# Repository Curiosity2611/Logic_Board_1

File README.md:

## Full Documentation

I will amend this documentation as the project progresses.

**Logic Board 1 Variants:**

- Logic Board 1A (No wireless)
	- LB1A_DCA7M4_R512MB_F4GB (Dual Core A7 + M4, 512MB DDR3L RAM, 4GB eMMC)
	- LB1A_SCA7M4_R512MB_F4GB (Single Core A7 + M4, 512MB DDR3L RAM, 4GB eMMC)
- Logic Board 1B (Only BLE 5.0)
	- LB1B_DCA7M4_R512MB_F4GB (Dual Core A7 + M4, 512MB DDR3L RAM, 4GB eMMC)
	- LB1B_SCA7M4_R512MB_F4GB (Single Core A7 + M4, 512MB DDR3L RAM, 4GB eMMC)
- Logic Board 1C (Only WiFi)
	- LB1B_DCA7M4_R512MB_F4GB (Dual Core A7 + M4, 512MB DDR3L RAM, 4GB eMMC)
	- LB1B_SCA7M4_R512MB_F4GB (Single Core A7 + M4, 512MB DDR3L RAM, 4GB eMMC)
- Logic Board 1D (WiFi + BLE 5.0)
	- LB1B_DCA7M4_R512MB_F4GB (Dual Core A7 + M4, 512MB DDR3L RAM, 4GB eMMC)
	- LB1B_SCA7M4_R512MB_F4GB (Single Core A7 + M4, 512MB DDR3L RAM, 4GB eMMC)

**Logic Board I/O:**

Common expansion Board for all Logic Board 1 Variants. 

## A little background about the project

How it all started.

### Problem

Recently I came accross the ST's line of Microprocessors and I felt it fascinating. I personally felt this is one of the best Microprocessor out there in the market as it is the combination of an MPU and an  MCU. This combination has many use cases and I felt I should try this out. So I bought STM32MP157C-DK2 development board and started experimenting! <br>

Previously I had little experience working on couple of popular linux dev boards like the BeagleBone Black
and the Raspberry Pi. They are both fantastic boards to work with and they both have good community support. But while working with them, I realised a few bunch of problems:

- **Raspberry Pi Compute Module 4 + IO Board**
    - CM4 is easy to use but not ideal for mass production.
    - No support for analog signals at hardware level.
    - Software PWM possible but not very precise.
    - Cannot support real time application or processing.
    - Not fully open-source and very minimum customization possible. <br>
<br>

- **BeagleBone Black**
    - Easy to use but user has to own build hardware for production.
    - PRUs make RT applications possible but super difficult to use.
    - Cannot support MIPI-DSI and HD graphics.
    - Programming PRUs is not an easy task.

### Solution

**Best of both worlds**

**Hello World STM32MP1 !!**

- Board design inspired from Raspberry Pi Compute Module 4 and CM4 IO board.
- Operating system derived from Beaglebone Black with implementation of Bonescript Library and Cloud9 IDE.
- Footprint compatible Single or dual Cortex-A7 Processors + dedicated Cortex-M4 core for real-time and low-power applications.
- Support for MIPI-DSI display for HMI applications.
- Fully open-source Hardware and Software.

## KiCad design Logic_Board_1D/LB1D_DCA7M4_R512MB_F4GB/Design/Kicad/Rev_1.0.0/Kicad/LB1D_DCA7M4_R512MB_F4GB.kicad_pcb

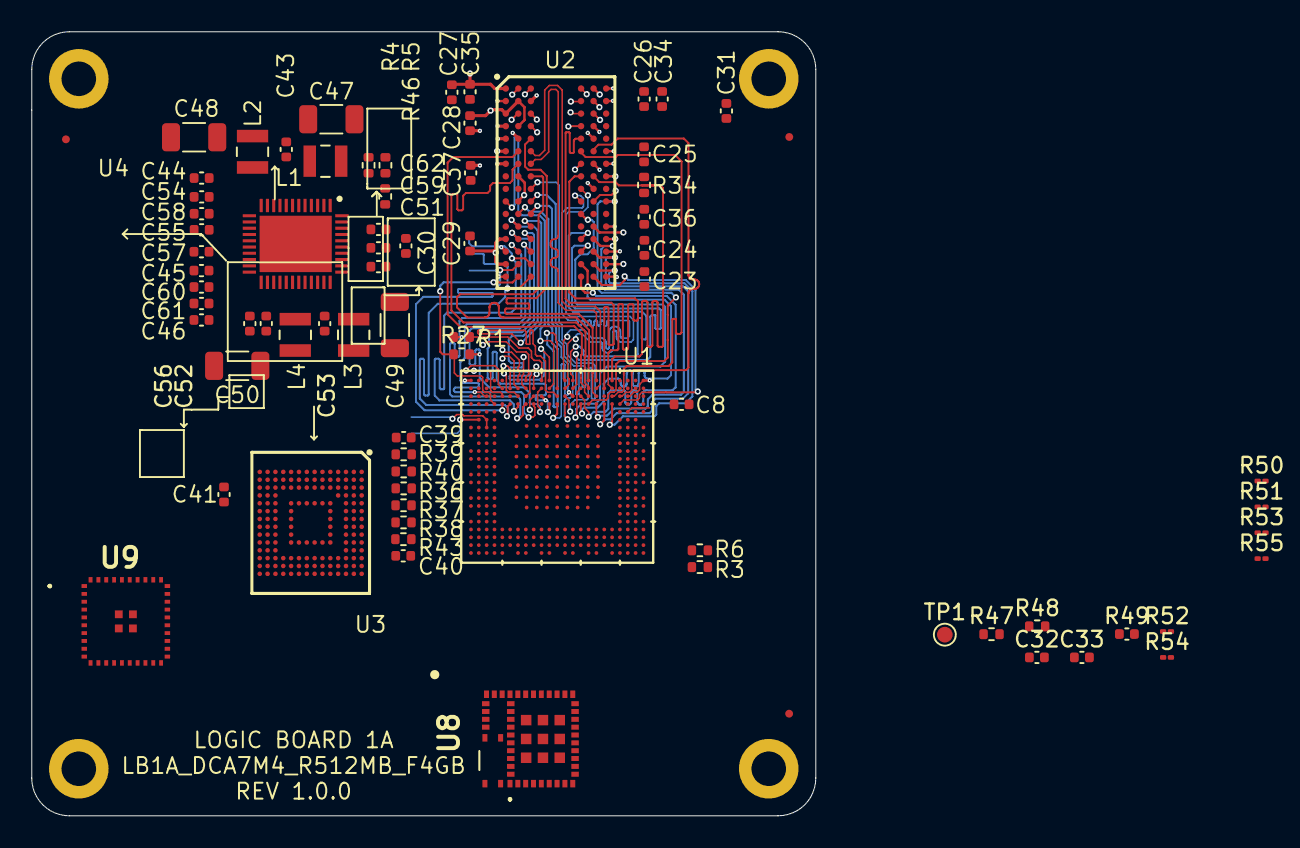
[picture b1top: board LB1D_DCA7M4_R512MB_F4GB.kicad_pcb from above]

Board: 4 copper layers, 50.0 x 50.0 mm, 157 parts (0 on the bottom side), 213 nets.

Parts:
C1, C2, C5, C6, C51, C52, C63, C64, C65, C66, C67, C68, C69, C70, C72, C73, C74: 1uF; C_0402_1005Metric
C3, C4, C8, C9, C10, C11, C12, C13, C14, C15, C16, C17, C18, C19, C20, C23, C24, C25, C26, C27, C28, C29, C30, C31, C36, C37, C38, C39, C40: 100nF; C_0402_1005Metric
C7: 10nF; C_0402_1005Metric
C21, C22, C32, C34, C35, C41, C43, C44, C45, C46, C54: 10uF; C_0402_1005Metric
C33, C75, C76, C77: 10pF; C_0402_1005Metric
C42: 2.2uF; C_0402_1005Metric
C47, C48, C49, C50: 22uF; C_1206_3216Metric
C53, C55, C56, C57, C58, C59, C60, C61, C62: 4.7uF; C_0402_1005Metric
FID1, FID2, FID3, FID4, FID5, FID6: Fiducial; Fiducial_0.5mm_Mask1.5mm
H1, H2, H3, H4: MountingHole_Pad; MountingHole_2.2mm_M2_DIN965_Pad
L1, L2, L3, L4: 1uH; MGV2520101R0M-10
R1, R34: 240E; R_0402_1005Metric
R2, R3, R4, R5: 1k5; R_0402_1005Metric
R6, R27, R35, R46: 10k; R_0402_1005Metric
R7: 3k; R_0402_1005Metric
R8, R9, R10, R11, R12, R13, R14, R15, R16, R17, R18, R19, R20, R21, R22, R23, R24, R25, R28, R29, R30, R31, R32, R33: 56E; R_0402_1005Metric
R26, R47, R48: 100E; R_0402_1005Metric
R36, R37, R38, R39, R40, R41, R42, R43, R44, R45: 47k; R_0402_1005Metric
R49: 0E; C_0402_1005Metric
R50, R51, R52, R53, R54, R55: 100k; C_01005_0402Metric
TP1: TestPoint; TestPoint_Pad_D1.0mm
U1: STM32MP157CAC3
U2: AS4C256M16D3LC-12BCN
U3: S40FC004C1B2C00000
U4: STPMIC1BPQR
U5, U6, U7: DF40C-70DP-0.4V(51); DF40C70DP04V51
U8: WFM200S022XNA3R; WFM200S022XNA3
U9: BGX220S22HNA21R; BGX220S22HNA21
X1: 32.768kHz; SiT1533AC-H5-DCC-32.768E
X2: 24MHz; TSX3225240000MF10ZC3

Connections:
5V_VIN: C43.1, C44.1, C45.1, C46.1, C51.1, C52.1, C53.1, U4.8, U4.12, U4.19, U4.22, U4.24, U4.28, U4.36, U6.2, U6.4, U6.6, U6.8, U6.10
ANA0: U1.U3, U7.31
ANA1: U1.U4, U7.33
BLE_RESET: U1.Y5, U9.35
BOOT0: U1.N1, U5.37
BOOT1: U1.N4, U5.25
BOOT2: U1.M2, U5.41
DDR_A0: R8.2, U1.L20, U2.N3
DDR_A1: R9.2, U1.P22, U2.P7
DDR_A2: R10.2, U1.J20, U2.P3
DDR_A3: R11.2, U1.K22, U2.N2
DDR_A4: R12.2, U1.V20, U2.P8
DDR_A5: R13.2, U1.H20, U2.P2
DDR_A6: R14.2, U1.W20, U2.R8
DDR_A7: R15.2, U1.E20, U2.R2
DDR_A8: R16.2, U1.Y20, U2.T8
DDR_A9: R17.2, U1.G20, U2.R3
DDR_A10: R18.2, U1.R22, U2.L7
DDR_A11: R19.2, U1.R20, U2.R7
DDR_A12: R20.2, U1.P23, U2.N7
DDR_A13: R21.2, U1.F20, U2.T3
DDR_A14: R22.2, U1.R21, U2.T7
DDR_BA0: R23.2, U1.L23, U2.M2
DDR_BA1: R24.2, U1.U20, U2.N8
DDR_BA2: R25.2, U1.M21, U2.M3
DDR_CASN: R33.2, U1.N20, U2.K3
DDR_CKE: R28.1, R35.2, U1.T20, U2.K9
DDR_CLK_N: R26.1, U1.N23, U2.K7
DDR_CLK_P: R26.2, U1.N22, U2.J7
DDR_CSN: R30.1, U1.M22, U2.L2
DDR_DQ0: U1.E22, U2.A2
DDR_DQ1: U1.F22, U2.C3
DDR_DQ2: U1.H21, U2.A7
DDR_DQ3: U1.E21, U2.C2
DDR_DQ4: U1.J21, U2.B8
DDR_DQ5: U1.J22, U2.C8
DDR_DQ6: U1.H22, U2.D7
DDR_DQ7: U1.G21, U2.A3
DDR_DQ8: U1.T21, U2.F2
DDR_DQ9: U1.U21, U2.E3
DDR_DQ10: U1.T22, U2.G2
DDR_DQ11: U1.W21, U2.F7
DDR_DQ12: U1.W23, U2.H8
DDR_DQ13: U1.T23, U2.H3
DDR_DQ14: U1.W22, U2.H7
DDR_DQ15: U1.Y21, U2.F8
DDR_DQM0: U1.H23, U2.D3
DDR_DQM1: U1.V22, U2.E7
DDR_DQS0_N: U1.G23, U2.B7
DDR_DQS0_P: U1.G22, U2.C7
DDR_DQS1_N: U1.U23, U2.G3
DDR_DQS1_P: U1.U22, U2.F3
DDR_ODT: R31.2, U1.L22, U2.K1
DDR_RASN: R29.2, U1.N21, U2.J3
DDR_RESETN: R27.2, U1.D20, U2.T2
DDR_WEN: R32.1, U1.M20, U2.L3
DSI_BL_CTRL: U1.AA19, U7.70
DSI_CKN: U1.A16, U5.56
DSI_CKP: U1.B16, U5.58
DSI_D0_N: U1.B15, U5.18
DSI_D0_P: U1.C15, U5.54
DSI_D1_N: U1.A17, U5.60
DSI_D1_P: U1.B17, U5.62
DSI_LCD_INT: U1.A14, U5.14
DSI_RESET: U1.D19, U5.36
DSI_TE: U1.B14, U5.16
ETH_CLK: U1.Y8, U7.48
ETH_CLK125: U1.Y6, U7.32
ETH_GTX_CLK: U1.AB2, U7.20
ETH_MDC: U1.AA6, U7.28
ETH_MDINT: U1.AC8, U7.46
ETH_MDIO: U1.AC3, U7.22
ETH_NRST: R6.1, U1.AC2, U7.18
ETH_RXD0: U1.AC7, U7.42
ETH_RXD1: U1.AB7, U7.38
ETH_RXD2: U1.AB6, U7.36
ETH_RXD3: U1.W4, U7.51
ETH_RX_CLK: U1.AA4, U7.16
ETH_RX_DV: U1.AB8, U7.44
ETH_TXD0: U1.AA2, U7.49
ETH_TXD1: U1.AA1, U7.43
ETH_TXD2: U1.Y2, U7.41
ETH_TXD3: U1.Y1, U7.39
ETH_TX_EN: U1.AB1, U7.45
GND: C1.2, C2.2, C3.2, C4.2, C5.1, C6.2, C7.2, C8.2, C9.2, C10.2, C11.2, C12.2, C13.2, C14.2, C15.2, C16.2, C17.2, C18.2, C19.2, C20.2, C21.2, C22.2, C23.2, C24.2, C25.2, C26.2, C27.2, C28.2, C29.2, C30.2, C31.2, C32.1, C33.1, C34.2, C35.2, C36.2, C37.2, C38.2, C39.2, C40.2, C41.2, C42.2, C43.2, C44.2, C45.2, C46.2, C47.2, C48.2, C49.2, C50.2, C51.2, C52.2, C53.2, C54.2, C55.2, C56.2, C57.2, C58.2, C59.2, C60.2, C61.2, C62.2, C63.2, C64.2, C65.2, C66.2, C67.2, C68.2, C69.2, C70.2, C72.2, C73.2, C74.2, C75.1, C76.1, C77.1, R1.2, R7.2, R27.1, R34.2, R35.1, R47.2, R48.2, U1.1A3, U1.1A5, U1.1A7, U1.1B2, U1.1B4, U1.1B6, U1.1B8, U1.1C1, U1.1C3, U1.1C5, U1.1C7, U1.1C9, U1.1D2, U1.1D4, U1.1D6, U1.1D8, U1.1E1, U1.1E3, U1.1E5, U1.1E7, U1.1E9, U1.1F2, U1.1F4, U1.1F6, U1.1F8, U1.1G1, U1.1G3, U1.1G5, U1.1G7, U1.1G9, U1.1H2, U1.1H4, U1.1H6, U1.1H8, U1.1J3, U1.1J5, U1.1J7, U1.A1, U1.A23, U1.AA5, U1.AA8, U1.AA12, U1.AA16, U1.AA21, U1.AB13, U1.AC1, U1.AC23, U1.C7, U1.C12, U1.C16, U1.C21, U1.D4, U1.F21, U1.H3, U1.K21, U1.L1, U1.P3, U1.P21, U1.V21, U1.W3, U2.A9, U2.B1, U2.B3, U2.B9, U2.D1, U2.D8, U2.E1, U2.E2, U2.E8, U2.F9, U2.G1, U2.G8, U2.G9, U2.J2, U2.J8, U2.M1, U2.M9, U2.P1, U2.P9, U2.T1, U2.T9, U3.A6, U3.C4, U3.D3, U3.E2, U3.E7, U3.F1, U3.G5, U3.H10, U3.J5, U3.K8, U3.N2, U3.N5, U3.P1, U3.P4, U3.P6, U4.6, U4.10, U4.15, U4.26, U4.30, U4.32, U4.41, U4.ep, U6.27, U6.29, U6.31, U6.33, U6.35, U6.61, U6.62, U6.63, U6.64, U6.65, U6.66, U6.67, U6.68, U6.69, U6.70, U8.1, U8.4, U8.5, U8.6, U8.7, U8.8, U8.11, U8.18, U8.21, U8.33, U8.35, U8.36, U8.39, U8.41, U8.42, U8.43, U8.44, U8.45, U8.46, U8.48, U8.49, U8.50, U8.51, U8.52, U8.53, U8.54, U8.55, U8.56, U8.57, U8.58, U9.4, U9.5, U9.36, U9.40, U9.41, U9.42, U9.43, U9.44, X1.2, X2.2, X2.4
HDMI_CEC: U1.Y14, U7.53
HDMI_INT: U1.W1, U7.37
HDMI_NRST: U1.Y17, U7.65
I2C1_SCL: R2.1, U1.Y18, U7.67
I2C1_SDA: R3.1, U1.Y4, U7.47
I2C4_SCL: R4.1, U1.G2, U4.4, U5.29
I2C4_SDA: R5.1, U1.H2, U4.3, U5.31
I2S2_CK: U1.D14, U5.24
I2S2_SDO: U1.E1, U5.57
I2S2_WS: U1.B10, U5.50
JTCK_SWCLK: U1.B20, U5.70
JTDI: U1.A20, U5.68
JTDO_TRACESWO: U1.A19, U5.64
JTMS_SWDIO: U1.C20, U5.34
LCD_B0: U1.K1, U5.53
LCD_B1: U1.K4, U5.45
LCD_B2: U1.AB11, U7.54
LCD_B3: U1.B5, U5.44
LCD_B4: U1.B4, U5.42
LCD_B5: U1.U2, U7.35
LCD_B6: U1.F4, U5.51
LCD_B7: U1.K3, U5.43
LCD_CLK: U1.AC14, U7.66
LCD_DE: U1.Y12, U7.50
LCD_G0: U1.AA7, U7.30
LCD_G1: U1.C10, U5.52
LCD_G2: U1.D1, U5.61
LCD_G3: U1.C3, U5.40
LCD_G4: U1.B1, U5.67
LCD_G5: U1.C1, U5.63
LCD_G6: U1.E3, U5.59
LCD_G7: U1.E2, U5.55
LCD_HSYNC: U1.T1, U7.27
LCD_R0: U1.AB4, U7.26
LCD_R1: U1.AA3, U7.14
LCD_R2: U1.D5, U5.12
LCD_R3: U1.C5, U5.10
LCD_R4: U1.C2, U5.65
LCD_R5: U1.AB5, U7.34
LCD_R6: U1.B2, U5.69
LCD_R7: U1.D3, U5.38
LCD_VSYNC: U1.H4, U5.47
MPU_VDDA_1V8_REG: C1.1, C4.1, U1.AB14, U1.C14
NJRST: U1.B19, U5.66
NRST: R46.2, U1.M3, U3.J1, U3.J2, U3.J3, U3.K5, U4.1, U5.33, U8.12
unnamed: C5.2, U1.C17, U1.C18
unnamed: C6.1, U1.AB15
unnamed: C7.1, U1.M4
unnamed: C33.2, U8.47
unnamed: C42.1, U3.C1, U3.C2
unnamed: C62.1, U4.40
unnamed: C75.2, U1.P2, X2.3
unnamed: C76.2, U1.P1, X2.1
unnamed: C77.2, U1.L2, X1.3
unnamed: L1.1, U4.7
unnamed: L2.1, U4.11
unnamed: L3.1, U4.29
unnamed: L4.1, U4.25
unnamed: R1.1, U1.K23
unnamed: R7.1, U1.AB18
unnamed: R34.1, U2.L8
unnamed: R47.1, R48.1, U8.9
unnamed: R49.1, U9.2
unnamed: R49.2, U9.3
unnamed: TP1.1, U9.25
unnamed: U8.2, U8.3
PA0_WKUP: U1.AB3, U4.43
PMIC_LDO1_1V8: C56.1, U4.23, U6.16, U6.18, U6.20, U6.22, U6.24
PMIC_LDO2_2V9: C57.1, U4.18, U6.30, U6.32, U6.34, U6.36
PMIC_LDO3_VTT_DDR: C9.1, C10.1, C11.1, C12.1, C13.1, C14.1, C15.1, C16.1, C17.1, C18.1, C19.1, C20.1, C21.1, C22.1, C58.1, R8.1, R9.1, R10.1, R11.1, R12.1, R13.1, R14.1, R15.1, R16.1, R17.1, R18.1, R19.1, R20.1, R21.1, R22.1, R23.1, R24.1, R25.1, R28.2, R29.1, R30.2, R31.1, R32.2, R33.1, U4.14
PMIC_LDO4_VDD_USB: C3.1, C59.1, U1.AA15, U1.AA17, U4.39
PMIC_LDO5_2V9: C38.1, C39.1, C40.1, C41.1, C60.1, R36.1, R37.1, R38.1, R39.1, R40.1, R41.1, R42.1, R43.1, R44.1, R45.1, U3.A9, U3.B8, U3.C6, U3.C7, U3.E6, U3.F5, U3.J10, U3.K9, U3.M4, U3.N4, U3.P3, U3.P5, U4.20, U6.51, U6.53
PMIC_LDO6_1V0: C61.1, U4.21, U6.42, U6.44, U6.46, U6.48
PMIC_VOUT1_VDD_CORE: C47.1, C63.1, C64.1, C65.1, C66.1, L1.2, U1.1A2, U1.1A4, U1.1A6, U1.1B1, U1.1B3, U1.1B5, U1.1C2, U1.1C4, U1.1C6, U1.1D1, U1.1D3, U1.1D5, U1.1D7, U1.1E2, U1.1E4, U1.1E6, U1.1F5, U1.1F7, U1.1G6, U1.1H7, U4.5
PMIC_VOUT2_VDD_DDR: C23.1, C24.1, C25.1, C26.1, C27.1, C28.1, C29.1, C30.1, C31.1, C34.1, C35.1, C48.1, C54.1, C72.1, C73.1, C74.1, L2.2, U1.1A8, U1.1B7, U1.1B9, U1.1C8, U1.1D9, U1.1E8, U1.1F9, U1.1G8, U1.1H9, U1.1J8, U2.A1, U2.A8, U2.B2, U2.C1, U2.C9, U2.D2, U2.D9, U2.E9, U2.F1, U2.G7, U2.H2, U2.H9, U2.K2, U2.K8, U2.N1, U2.N9, U2.R1, U2.R9, U4.9, U4.13
PMIC_VOUT3_VDD: C2.1, C49.1, C67.1, C68.1, C69.1, C70.1, L3.2, R2.2, R3.2, R4.2, R5.2, R6.2, R46.1, U1.1F1, U1.1F3, U1.1G2, U1.1G4, U1.1H1, U1.1H3, U1.1H5, U1.1J2, U1.1J4, U1.1J6, U1.B18, U1.R3, U1.R4, U1.T3, U4.31, U4.42, U6.15, U6.17, U6.19, U6.21, U6.23, X1.4
PMIC_VOUT4_3V3: C32.2, C50.1, L4.2, R50.1, R51.1, R52.1, R53.1, R54.1, R55.1, U4.27, U6.1, U6.3, U6.5, U6.7, U6.9, U8.10, U8.20, U8.28, U9.22, U9.23
PMIC_VREF_DDR: C8.1, C36.1, C37.1, C55.1, U1.AC20, U2.H1, U2.M8, U4.16
PMIC_WAKEUP: U1.K2, U4.2
POWER_ON: U1.R2, U4.44
SDMMC1_CK: U1.D13, U5.22
SDMMC1_CMD: U1.D12, U5.20
SDMMC1_D0: U1.D18, U5.32
SDMMC1_D1: U1.D17, U5.30
SDMMC1_D2: U1.D15, U5.26
SDMMC1_D3: U1.D16, U5.28
SDMMC2_CK: R45.2, U1.C9, U3.K1, U3.K2, U3.K3, U3.M6
SDMMC2_CMD: R44.2, U1.A10, U3.L1, U3.L2, U3.L3, U3.M5
SDMMC2_D0: R36.2, U1.C13, U3.A3
SDMMC2_D1: R37.2, U1.B12, U3.A4
SDMMC2_D2: R38.2, U1.A11, U3.A5
SDMMC2_D3: R39.2, U1.B13, U3.A1, U3.B2
SDMMC2_D4: R40.2, U1.AB10, U3.A2, U3.B3
SDMMC2_D5: R41.2, U1.A8, U3.B4, U3.C3, U3.D2, U3.E1
SDMMC2_D6: R42.2, U1.C11, U3.B5, U3.C5, U3.D4, U3.E3, U3.F2, U3.G1
SDMMC2_D7: R43.2, U1.B11, U3.A8, U3.B6, U3.B7
SDMMC3_CK: R50.2, U1.B7, U8.22
SDMMC3_CMD: R51.2, U1.A5, U8.23
SDMMC3_D0: R52.2, U1.D8, U8.24
SDMMC3_D1: R53.2, U1.D9, U8.25
SDMMC3_D2: R54.2, U1.D7, U8.26
SDMMC3_D3: R55.2, U1.D10, U8.27
SPI5_MISO: U1.AC11, U7.52
SPI5_MOSI: U1.AA14, U7.62
SPI5_NSS: U1.AA13, U7.64
SPI5_SCK: U1.AB12, U7.60
STLINK_UART4_RX: U1.B8, U5.46
STLINK_UART4_TX: U1.B9, U5.48
STUSB1600_IRQOUTn: U1.P4, U7.25
USART1_CTS: U1.G4, U5.49
USART1_RTS: U1.AB19, U7.69
USART1_RX: U1.Y16, U7.55
USART1_TX: U1.Y7, U7.40
USART3_CTS: U1.AC10, U9.16
USART3_RTS: U1.AB9, U9.17
USART3_RX: U1.AC5, U9.11
USART3_TX: U1.Y3, U9.15
USB_DM1: U1.AB17, U7.63
USB_DM2: U1.AB16, U7.59
USB_DP1: U1.AC17, U7.61
USB_DP2: U1.AC16, U7.57
U_BUTTON_1: U1.N2, U5.39
U_BUTTON_2: U1.T2, U7.29
U_LED_1: U1.L3, U5.35
U_LED_2: U1.AC4, U7.24
WIFI_IRQ: U1.A4, U8.19
WIFI_WKUP: U1.B3, U8.13
nPONKEY: U4.17, U5.27

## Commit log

2021-05-28 Placement Complete
2021-05-28 edited gitignore
2021-05-31 PCB completed upto connectors
2021-05-31 completed power connector
2021-06-01 working on connectors
2021-06-02 Fully Routed
2021-06-02 sch mods
2021-06-02 directory changes
2021-06-03 schematic verification completed
2021-06-04 improvements on sch and pcb
2021-06-05 some more improvements
2021-06-05 more improvements
2021-06-06 Improvements to PCB
2021-06-07 pcb improvements
2021-06-07 some more imps
2021-06-08 more imps
2021-06-08 more improvements on PCB
2021-06-09 improvements
2021-06-09 imps
2021-06-09 NO DRC & UNCONNECTED
2021-06-09 top layer done
2021-06-09 all layers done
2021-06-09 board shape donne
2021-06-09 top silkscreen completed
2021-06-10 bottom silkscreen completed
2021-06-10 silkscreen almost complete
2021-06-10 fab files added
2021-06-11 Logic Board 1D added
2021-06-11 Pcb routing

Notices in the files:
parts and their libraries:
Copyright 2016 Accelerated Designs. All rights reserved.
